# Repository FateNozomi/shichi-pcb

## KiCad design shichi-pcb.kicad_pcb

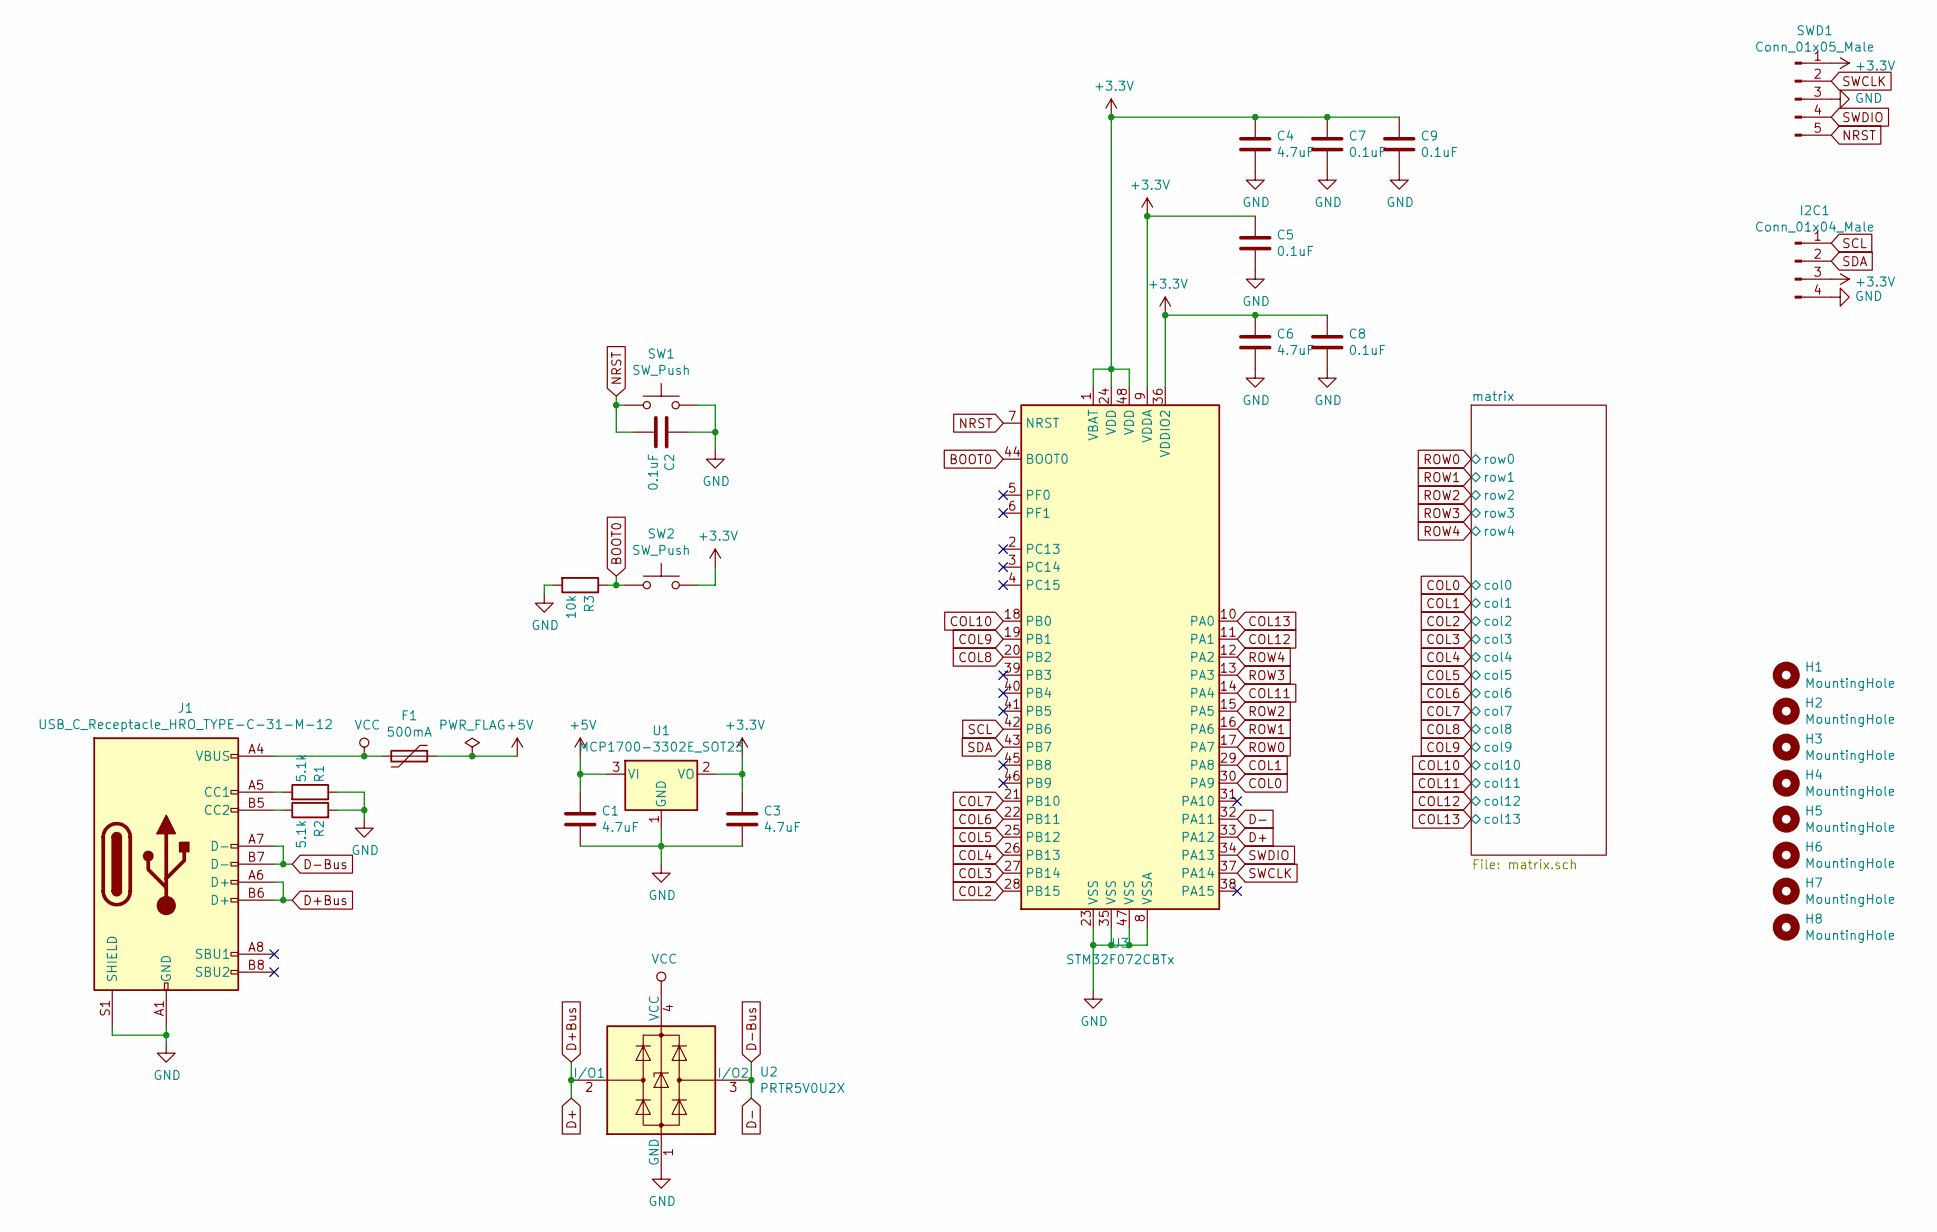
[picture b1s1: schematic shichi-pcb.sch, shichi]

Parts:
C1, C3, C4, C6: 4.7uF; C_0805_2012Metric_Pad1.15x1.40mm_HandSolder
C2, C5, C7, C8, C9: 0.1uF; C_0805_2012Metric_Pad1.15x1.40mm_HandSolder
F1: 500mA; Fuse_1206_3216Metric_Pad1.42x1.75mm_HandSolder
H1, H2, H3, H4, H5, H6, H7, H8: MountingHole; MountingHole_2.2mm_M2_Pad
I2C1: Conn_01x04_Male; I2C_Header_1x04_P2.54mm_Vertical
J1: USB_C_Receptacle_HRO_TYPE-C-31-M-12; USB_C_Receptacle_HRO_TYPE-C-31-M-12-HandSoldering
R1, R2: 5.1k; R_0805_2012Metric_Pad1.15x1.40mm_HandSolder
R3: 10k; R_0805_2012Metric_Pad1.15x1.40mm_HandSolder
SW1, SW2: SW_Push; SW_SPST_TL3342
SWD1: Conn_01x05_Male; SWD_Header_1x05_P2.54mm_Vertical
U1: MCP1700-3302E_SOT23; SOT-23
U2: PRTR5V0U2X; SOT-143
U3: STM32F072CBTx; LQFP-48_7x7mm_P0.5mm

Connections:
+3V3: C3.1, C4.1, C5.1, C6.1, C7.1, C8.1, C9.1, I2C1.3, SW2.2, SWD1.1, U1.2 (VO), U3.1 (VBAT), U3.9 (VDDA), U3.24 (VDD), U3.36 (VDDIO2), U3.48 (VDD); also elsewhere on the board
+5V: C1.1, F1.1, U1.3 (VI)
BOOT0: R3.1, SW2.1, U3.44 (BOOT0); also elsewhere on the board
COL0: U3.30 (PA9); also elsewhere on the board
COL1: U3.29 (PA8); also elsewhere on the board
COL2: U3.28 (PB15); also elsewhere on the board
COL3: U3.27 (PB14); also elsewhere on the board
COL4: U3.26 (PB13); also elsewhere on the board
COL5: U3.25 (PB12); also elsewhere on the board
COL6: U3.22 (PB11); also elsewhere on the board
COL7: U3.21 (PB10); also elsewhere on the board
COL8: U3.20 (PB2); also elsewhere on the board
COL9: U3.19 (PB1); also elsewhere on the board
COL10: U3.18 (PB0); also elsewhere on the board
COL11: U3.14 (PA4); also elsewhere on the board
COL12: U3.11 (PA1); also elsewhere on the board
COL13: U3.10 (PA0); also elsewhere on the board
D+: J1.A6 (D+), J1.B6 (D+), U2.2 (I/O1), U3.33 (PA12)
D-: J1.A7 (D-), J1.B7 (D-), U2.3 (I/O2), U3.32 (PA11)
GND: C1.2, C2.1, C3.2, C4.2, C5.2, C6.2, C7.2, C8.2, C9.2, I2C1.4, J1.A1 (GND), J1.A12 (GND), J1.S1 (SHIELD), R1.1, R2.2, R3.2, SW1.2, SWD1.3, U1.1 (GND), U2.1 (GND), U3.8 (VSSA), U3.23 (VSS), U3.35 (VSS), U3.47 (VSS); also elsewhere on the board
NRST: C2.2, SW1.1, SWD1.5, U3.7 (NRST); also elsewhere on the board
unnamed: J1.A5 (CC1), R1.2
unnamed: J1.B5 (CC2), R2.1
ROW0: U3.17 (PA7); also elsewhere on the board
ROW1: U3.16 (PA6); also elsewhere on the board
ROW2: U3.15 (PA5); also elsewhere on the board
ROW3: U3.13 (PA3); also elsewhere on the board
ROW4: U3.12 (PA2); also elsewhere on the board
SCL: I2C1.1, U3.42 (PB6)
SDA: I2C1.2, U3.43 (PB7)
SWCLK: SWD1.2, U3.37 (PA14)
SWDIO: SWD1.4, U3.34 (PA13)
VCC: F1.2, J1.A4 (VBUS), J1.A9 (VBUS), U2.4 (VCC)

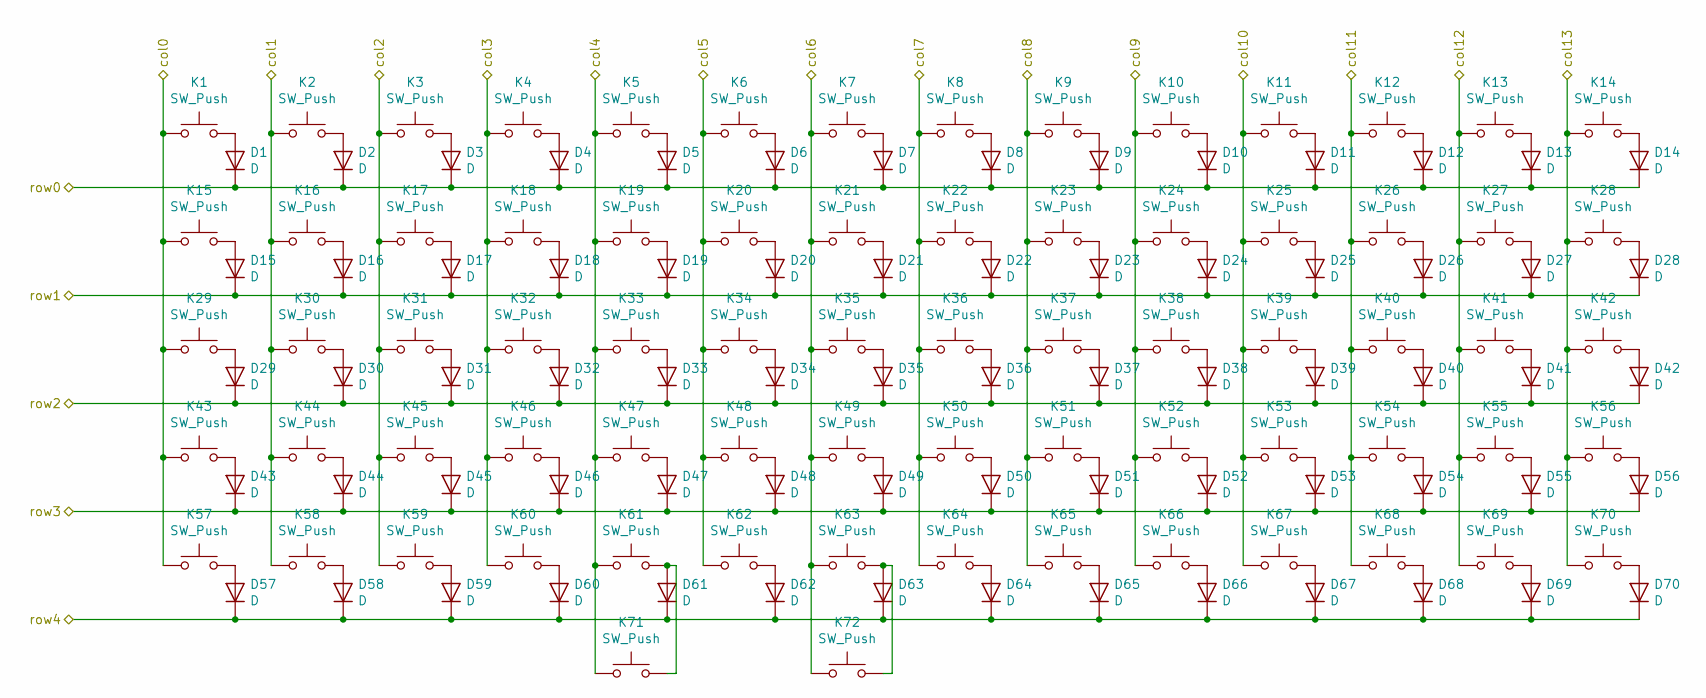
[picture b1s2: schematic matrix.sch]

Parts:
D1, D2, D3, D4, D5, D6, D7, D8, D9, D10, D11, D12, D13, D14, D15, D16, D17, D18, D19, D20, D21, D22, D23, D24, D25, D26, D27, D28, D29, D30, D31, D32, D33, D34, D35, D36, D37, D38, D39, D40, D41, D42, D43, D44, D45, D46, D47, D48, D49, D50, D51, D52, D53, D54, D55, D56, D57, D58, D59, D60, D61, D62, D63, D64, D65, D66, D67, D68, D69, D70: D; D_SOD-123
K1, K2, K3, K4, K5, K6, K7, K8, K9, K10, K11, K12, K13, K14, K15, K16, K17, K18, K19, K20, K21, K22, K23, K24, K25, K26, K27, K28, K29, K30, K31, K32, K33, K34, K35, K36, K37, K38, K39, K40, K41, K42, K43, K44, K45, K46, K47, K48, K49, K50, K51, K52, K53, K54, K55, K56, K57, K58, K59, K60, K61, K63, K64, K65, K66, K67, K68, K69, K70: SW_Push; MX_1.00u_PCB
K62: SW_Push; MX_7.00u_PCB_ReversedStabilizers
K71, K72: SW_Push; MX_2.00u_PCB_ReversedStabilizers

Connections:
COL0: K1.1, K15.1, K29.1, K43.1, K57.1; also elsewhere on the board
COL1: K2.1, K16.1, K30.1, K44.1, K58.1; also elsewhere on the board
COL2: K3.1, K17.1, K31.1, K45.1, K59.1; also elsewhere on the board
COL3: K4.1, K18.1, K32.1, K46.1, K60.1; also elsewhere on the board
COL4: K5.1, K19.1, K33.1, K47.1, K61.1, K71.1; also elsewhere on the board
COL5: K6.1, K20.1, K34.1, K48.1, K62.1; also elsewhere on the board
COL6: K7.1, K21.1, K35.1, K49.1, K63.1, K72.1; also elsewhere on the board
COL7: K8.1, K22.1, K36.1, K50.1, K64.1; also elsewhere on the board
COL8: K9.1, K23.1, K37.1, K51.1, K65.1; also elsewhere on the board
COL9: K10.1, K24.1, K38.1, K52.1, K66.1; also elsewhere on the board
COL10: K11.1, K25.1, K39.1, K53.1, K67.1; also elsewhere on the board
COL11: K12.1, K26.1, K40.1, K54.1, K68.1; also elsewhere on the board
COL12: K13.1, K27.1, K41.1, K55.1, K69.1; also elsewhere on the board
COL13: K14.1, K28.1, K42.1, K56.1, K70.1; also elsewhere on the board
unnamed: D1.2 (A), K1.2
unnamed: D2.2 (A), K2.2
unnamed: D3.2 (A), K3.2
unnamed: D4.2 (A), K4.2
unnamed: D5.2 (A), K5.2
unnamed: D6.2 (A), K6.2
unnamed: D7.2 (A), K7.2
unnamed: D8.2 (A), K8.2
unnamed: D9.2 (A), K9.2
unnamed: D10.2 (A), K10.2
unnamed: D11.2 (A), K11.2
unnamed: D12.2 (A), K12.2
unnamed: D13.2 (A), K13.2
unnamed: D14.2 (A), K14.2
unnamed: D15.2 (A), K15.2
unnamed: D16.2 (A), K16.2
unnamed: D17.2 (A), K17.2
unnamed: D18.2 (A), K18.2
unnamed: D19.2 (A), K19.2
unnamed: D20.2 (A), K20.2
unnamed: D21.2 (A), K21.2
unnamed: D22.2 (A), K22.2
unnamed: D23.2 (A), K23.2
unnamed: D24.2 (A), K24.2
unnamed: D25.2 (A), K25.2
unnamed: D26.2 (A), K26.2
unnamed: D27.2 (A), K27.2
unnamed: D28.2 (A), K28.2
unnamed: D29.2 (A), K29.2
unnamed: D30.2 (A), K30.2
unnamed: D31.2 (A), K31.2
unnamed: D32.2 (A), K32.2
unnamed: D33.2 (A), K33.2
unnamed: D34.2 (A), K34.2
unnamed: D35.2 (A), K35.2
unnamed: D36.2 (A), K36.2
unnamed: D37.2 (A), K37.2
unnamed: D38.2 (A), K38.2
unnamed: D39.2 (A), K39.2
unnamed: D40.2 (A), K40.2
unnamed: D41.2 (A), K41.2
unnamed: D42.2 (A), K42.2
unnamed: D43.2 (A), K43.2
unnamed: D44.2 (A), K44.2
unnamed: D45.2 (A), K45.2
unnamed: D46.2 (A), K46.2
unnamed: D47.2 (A), K47.2
unnamed: D48.2 (A), K48.2
unnamed: D49.2 (A), K49.2
unnamed: D50.2 (A), K50.2
unnamed: D51.2 (A), K51.2
unnamed: D52.2 (A), K52.2
unnamed: D53.2 (A), K53.2
unnamed: D54.2 (A), K54.2
unnamed: D55.2 (A), K55.2
unnamed: D56.2 (A), K56.2
unnamed: D57.2 (A), K57.2
unnamed: D58.2 (A), K58.2
unnamed: D59.2 (A), K59.2
unnamed: D60.2 (A), K60.2
unnamed: D61.2 (A), K61.2, K71.2
unnamed: D62.2 (A), K62.2
unnamed: D63.2 (A), K63.2, K72.2
unnamed: D64.2 (A), K64.2
unnamed: D65.2 (A), K65.2
unnamed: D66.2 (A), K66.2
unnamed: D67.2 (A), K67.2
unnamed: D68.2 (A), K68.2
unnamed: D69.2 (A), K69.2
unnamed: D70.2 (A), K70.2
ROW0: D1.1 (K), D2.1 (K), D3.1 (K), D4.1 (K), D5.1 (K), D6.1 (K), D7.1 (K), D8.1 (K), D9.1 (K), D10.1 (K), D11.1 (K), D12.1 (K), D13.1 (K), D14.1 (K); also elsewhere on the board
ROW1: D15.1 (K), D16.1 (K), D17.1 (K), D18.1 (K), D19.1 (K), D20.1 (K), D21.1 (K), D22.1 (K), D23.1 (K), D24.1 (K), D25.1 (K), D26.1 (K), D27.1 (K), D28.1 (K); also elsewhere on the board
ROW2: D29.1 (K), D30.1 (K), D31.1 (K), D32.1 (K), D33.1 (K), D34.1 (K), D35.1 (K), D36.1 (K), D37.1 (K), D38.1 (K), D39.1 (K), D40.1 (K), D41.1 (K), D42.1 (K); also elsewhere on the board
ROW3: D43.1 (K), D44.1 (K), D45.1 (K), D46.1 (K), D47.1 (K), D48.1 (K), D49.1 (K), D50.1 (K), D51.1 (K), D52.1 (K), D53.1 (K), D54.1 (K), D55.1 (K), D56.1 (K); also elsewhere on the board
ROW4: D57.1 (K), D58.1 (K), D59.1 (K), D60.1 (K), D61.1 (K), D62.1 (K), D63.1 (K), D64.1 (K), D65.1 (K), D66.1 (K), D67.1 (K), D68.1 (K), D69.1 (K), D70.1 (K); also elsewhere on the board

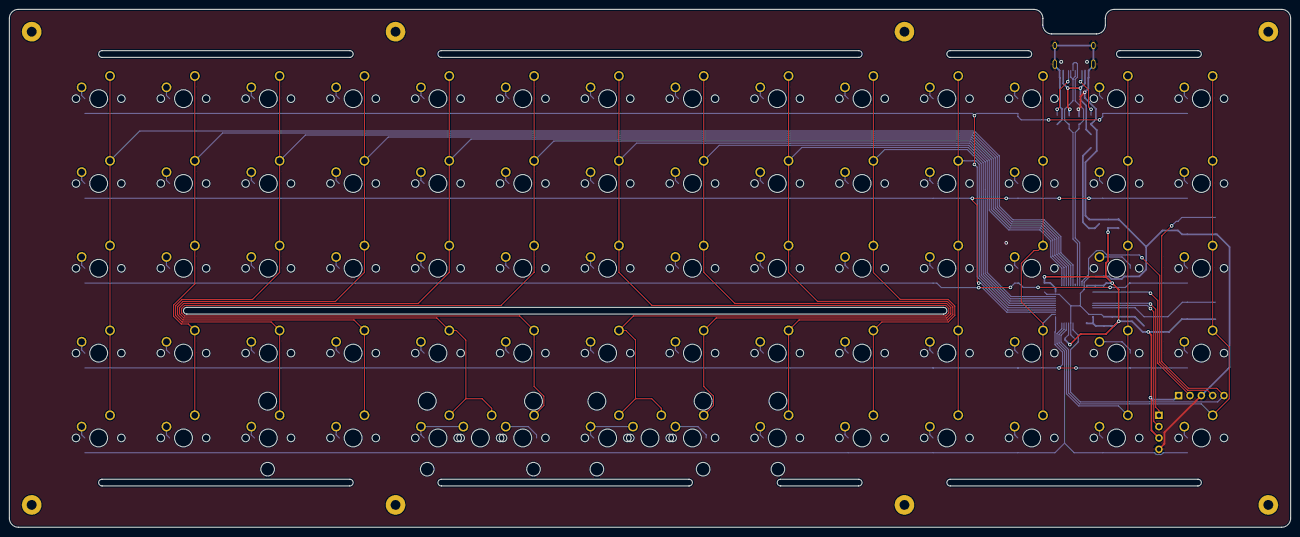
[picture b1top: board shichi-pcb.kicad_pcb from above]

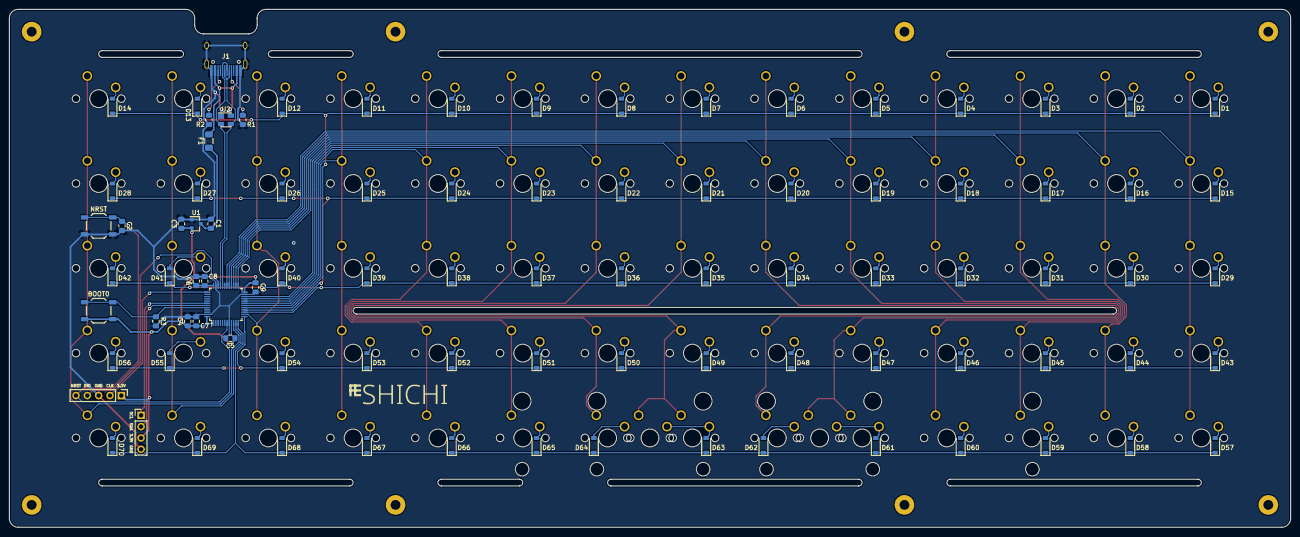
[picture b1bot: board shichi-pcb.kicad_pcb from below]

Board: 2 copper layers, 287.0 x 116.0 mm, 171 parts (91 on the bottom side), 103 nets.

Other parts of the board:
BOOT0: SW_Push; SW_SPST_TL3342
NRST: SW_Push; SW_SPST_TL3342

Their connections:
+3V3: BOOT0.2; also elsewhere on the board
BOOT0: BOOT0.1; also elsewhere on the board
GND: NRST.2; also elsewhere on the board
NRST: NRST.1; also elsewhere on the board

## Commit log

2019-06-07 Assign PCB footprints to schematic symbols
2019-06-07 Use custom symbol for USB C Receptacle USB C Receptacle from 5.1.2 symbol library VBUS and GND are set to power input instead of power output
2019-06-07 Fix XTAL1 ground short
2019-06-08 Use vertical group headers instead of individual headers
2019-06-08 Ground XTAL capacitors
2019-06-09 Optimize matrix pinout
2019-06-11 Add breakouts for unused pins
2019-06-12 Initial PCB layout design
2019-06-12 Implement over-current protection using polyfuse
2019-06-12 Add polyfuse to PCB layout design
2019-06-29 Make ESD protection component mandatory in schematic
2019-06-29 Update PCB layout tracks for ESD Protection
2019-06-30 Initial port of STM32F072 arm processor
2019-06-30 Assign PCB Footprints to new additional schematics
2019-07-05 Remove 22 ohm resistors from data lines
    Stated in the STM32F072CB datasheet P.99:
    No external termination series resistors are required on USB_DP (D+) and USB_DM (D-);
    the matching impedance is already included in the embedded driver.
2019-07-05 Replace MCP1825S with MCP1700-3302E LDO voltage regulator
2019-07-05 Optimize STM32F072 matrix pinout
2019-07-05 Flip serial wire debugging header pins
2019-07-06 Swap ROW3 and ROW4 pins to reposition diode D50
2019-07-07 Initial arm PCB layout design
2019-07-07 Remove NRST pull-up resistor
    The NRST pin input driver uses the CMOS technology. It is connected to a permanent pullup resistor, RPU
2019-07-07 Add mounting holes
2019-07-07 Add NRST and BOOT0 switch labels on B.SilkS
2019-07-07 Add GND filled zone on F.CU and B.Cu
2019-07-07 Remove mounting hole references on F.SilkS
2019-07-07 Plot v1.0 gerber files for fabrication
2019-07-12 Remove unused pin labels on silk screen layer
2019-07-22 Fix D+ and D- label swapped
2019-07-22 Increase ground copper zone clearance
2019-10-19 Plot v1.1 gerber files for fabrication
2019-10-20 Remove USB headers
2019-10-20 Remove B14 and B15 pin headers
2019-10-20 Remove AUDIO components
2019-10-20 Add *.sch-bak to .gitignore
2019-10-20 Replace all MX switch footprint to through-hole solder variant
2019-10-20 Change bottom row to support 6.25u spacebar
2019-10-20 Change USBLC6-2SC6 ESD protection device to PRTR5V0U2AX
2019-10-21 Replace 6.25u with 7.00u spacebar support
2019-11-03 Update PCB layout design to v2
2019-11-03 Reposition diode reference text
2019-11-03 Add shichi logo
2019-11-03 Plot v2.0 gerber files for fabrication
2019-12-31 Move external libraries dependencies to project specific
